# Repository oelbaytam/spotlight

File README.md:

# Spotlight

## What does it even do?
Spotlight is an [MQTT](https://learn.sparkfun.com/tutorials/introduction-to-mqtt/all) activated semi-high power LED (3.3-3.6V @715mA). It connects to MQTT Brokers (stay tuned for an MQTT discord bot!!) and uses the signal recieved to enable a PWM output to the LED. If I get it working correctly then there will be an enclosure with a way to focus the beam and some additional lenses to project imagery onto your wall or ceiling (think Bat-Signal). There are no physical inputs on the device so this is not a lamp.

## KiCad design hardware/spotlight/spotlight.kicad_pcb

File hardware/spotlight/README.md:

# The Spotlight Hardware

Spotlight is my first attempt at SMD soldering, PCB design, Circuitry implementing an IC, and many other smaller things, so bear with any mistakes I make and feel free to contribute if you have hardware knowledge! \
(Make sure you teach me something if you submit a PR >:] )

## The Schematic and PCB
##### Fraud at a glance?

### The ICs
- AL8841MP-13 \
  A buck converter stepping down the 5V input to ~714mA constant current configured by the 0.14Ohm sense resistor. The LED I am using is 5W and expects 3.6V at 1.2A but in my testing it was plenty bright at 700mA@3.3V so I decided that it will live its life at 3W (heatsinks really drove up the price per unit).
- AMS1117-3.3 \
  LDO regulator that provides 3.3V to the MCU.
- ESP32-C3-WROOM-02-N4 \
  Before its a hardware project this was initially an embedded project so I could learn RTOS, MQTT, and the ESP-IDF development framework! I went with the WROOM because I only planned on using one GPIO pin. The C3 MINI was a bit cheaper but had a lot of much smaller pads that I wasn't confident I could reflow. (Probably could've added some extra pins but I didn't wanna overcomplicate any more.)

### The Cool Image on the Back?!
The picture is an item icon in DEADLOCK (I <3 Deadlock) called [Boundless Spirit](https://deadlock.wiki/Boundless_Spirit). It has nothing to do with the project, just a cool stamp I snatched. I put it through some image dithering so that it can work with the silkscreen, when I get the first PCBs in I will put a picture of it to show the real world result.

# Assembling the device
I don't know yet, but I have a plan that I will share with anyone who is new so assembly can be easy and cheap, I am pinching as many pennies as possible with this project. (Possibly will make a video?)

### Parts List

As of now, to get flashbanged, all you need is:
- The materials in the BOM (in the ./production folder but I would export it yourself)
- 3.3V LED that wont die taking 750mA (technically the size doesn't matter yet since I don't have an enclosure made.)
- JST XH-2 connector with a cable
- a Heatsink for the LED, I am going to use a 40x40x11mm heatsink. 
I am going to put my bead LED on a little star aluminum PCB to make my life easier and to make heat transfer to the heatsink better.

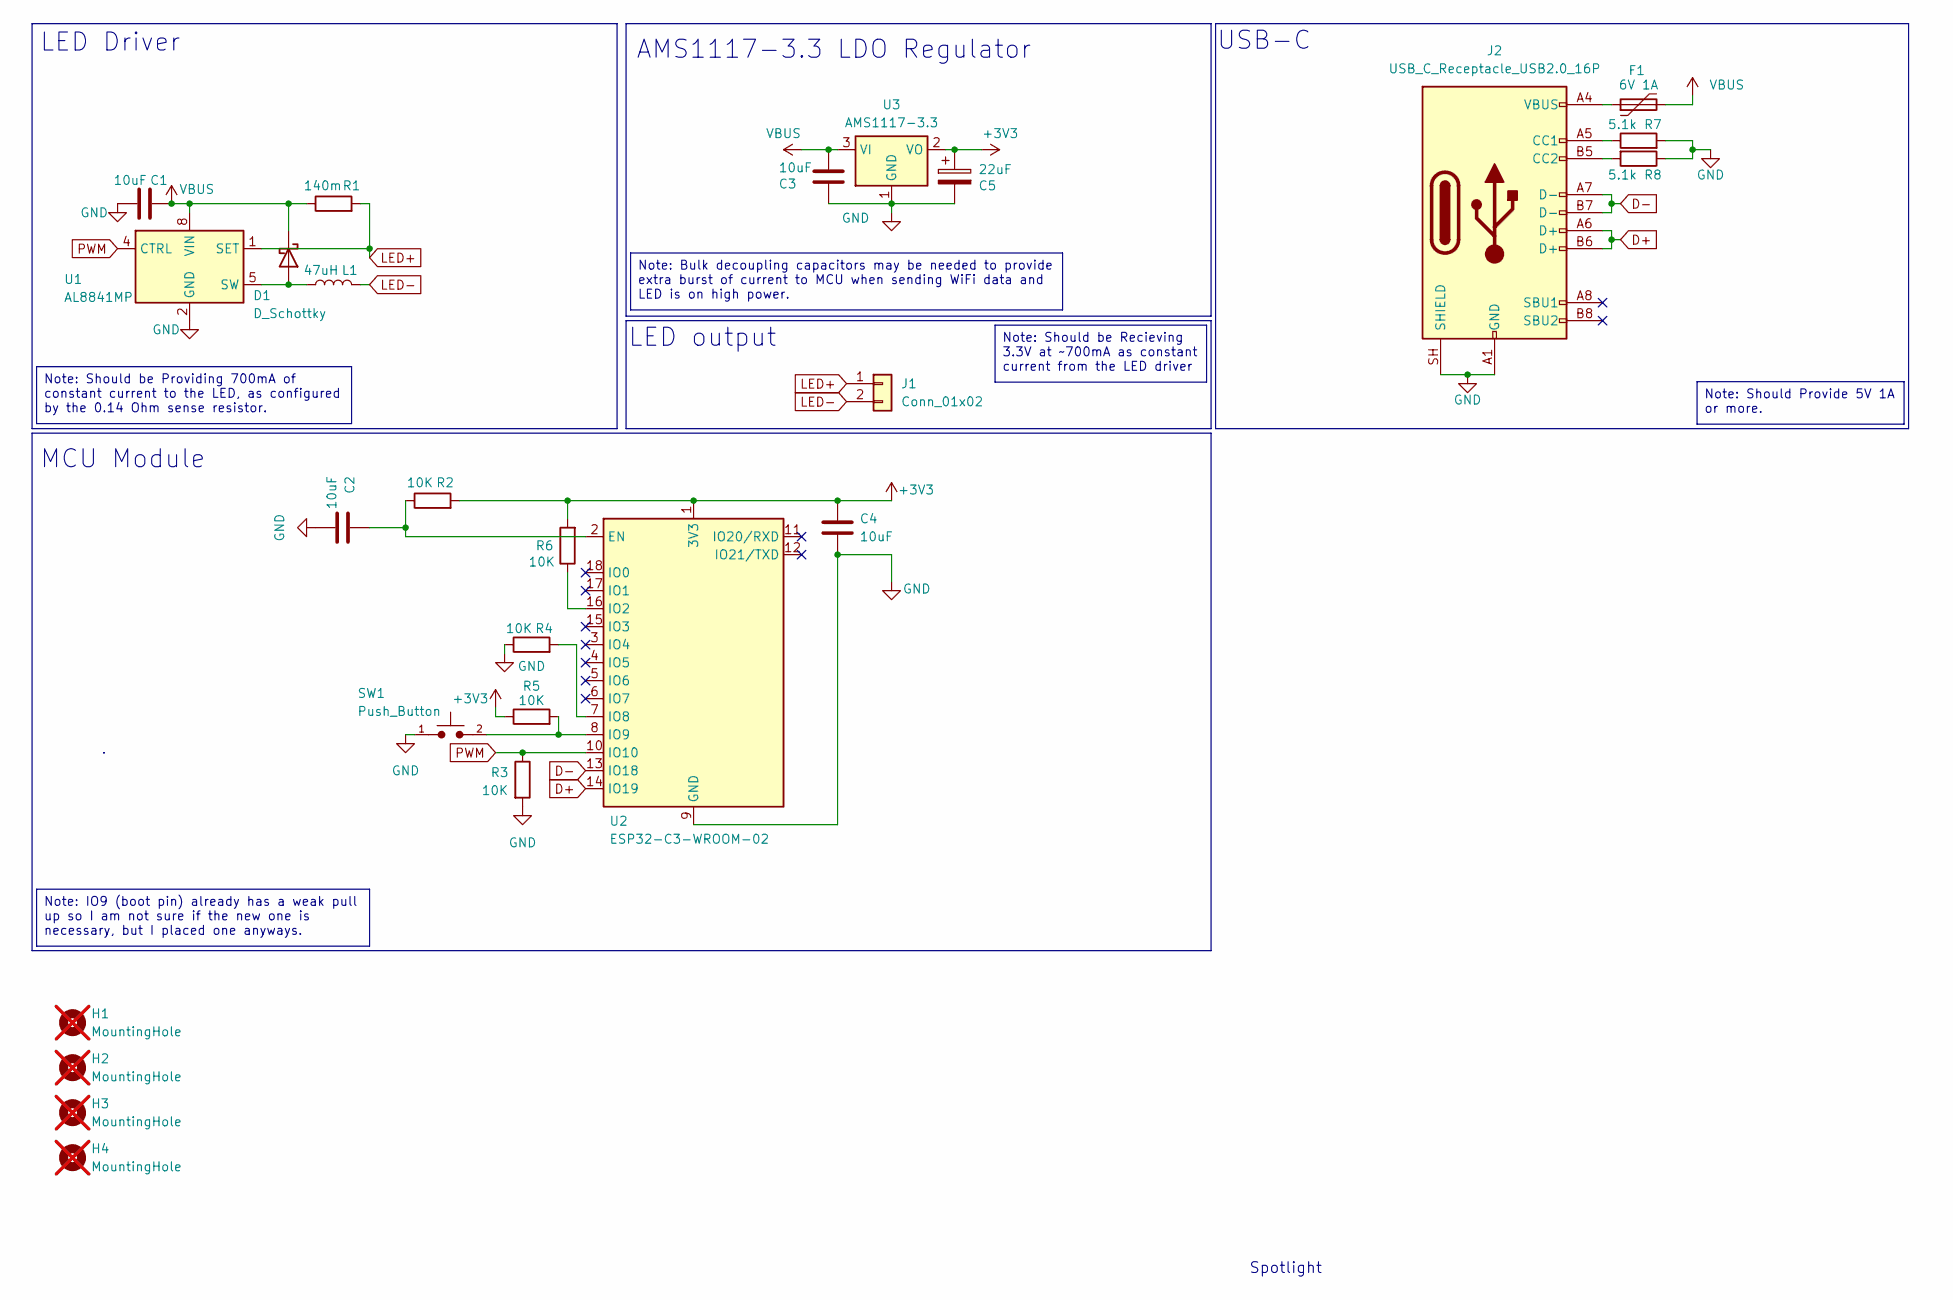
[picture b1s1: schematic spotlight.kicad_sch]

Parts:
C1, C2, C3, C4: 10uF; C_0603_1608Metric
C5: 22uF; C_1206_3216Metric
D1: D_Schottky; D_SOD-123F
F1: 6V 1A; R_0805_2012Metric
H1, H2, H3, H4: MountingHole; MountingHole_2.1mm; not fitted
J1: Conn_01x02; JST_XH_B2B-XH-A_1x02_P2.50mm_Vertical
J2: USB_C_Receptacle_USB2.0_16P; USB_C_Receptacle_XKB_U262-16XN-4BVC11
L1: 47uH; L_Chilisin_BWVS00606020
R1: 140m; R_1206_3216Metric
R2, R3, R4, R5, R6: 10K; R_0603_1608Metric
R7, R8: 5.1k; R_0603_1608Metric
SW1: Push_Button; SW_SPST_Omron_B3F-315x_Angled
U1: AL8841MP; MSOP-8-1EP_3x3mm_P0.65mm_EP1.5x1.8mm
U2: ESP32-C3-WROOM-02
U3: AMS1117-3.3; SOT-223-3_TabPin2

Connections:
+3V3: C4.1, C5.1, R2.2, R5.1, R6.2, U2.1 (3V3), U3.2 (VO)
D+: J2.A6 (D+), J2.B6 (D+), U2.14 (IO19)
D-: J2.A7 (D-), J2.B7 (D-), U2.13 (IO18)
GND: C1.2, C2.2, C3.2, C4.2, C5.2, J2.A1 (GND), J2.A12 (GND), J2.B1 (GND), J2.B12 (GND), J2.SH (SHIELD), R3.2, R4.1, R7.2, R8.1, SW1.1, U1.2 (GND), U1.3 (GND), U1.9 (GND), U2.9 (GND), U2.19 (GND), U3.1 (GND)
LED+: J1.1, R1.2, U1.1 (SET)
LED-: J1.2, L1.2
unnamed: D1.2 (A), L1.1, U1.5 (SW), U1.6 (SW)
unnamed: F1.1, J2.A4 (VBUS), J2.A9 (VBUS), J2.B4 (VBUS), J2.B9 (VBUS)
unnamed: J2.A5 (CC1), R7.1
unnamed: J2.B5 (CC2), R8.2
unnamed: C2.1, R2.1, U2.2 (EN)
unnamed: R6.1, U2.16 (IO2)
unnamed: R4.2, U2.7 (IO8)
unnamed: R5.2, SW1.2, U2.8 (IO9)
PWM: R3.1, U1.4 (CTRL), U2.10 (IO10)
VBUS: C1.1, C3.1, D1.1 (K), F1.2, R1.1, U1.8 (VIN), U3.3 (VI)

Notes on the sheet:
LED output
AMS1117-3.3 LDO Regulator
MCU Module
Spotlight
USB-C
LED Driver
Note: Bulk decoupling capacitors may be needed to provide extra burst of current to MCU when sending WiFi data and LED is on high power.
Note: IO9 (boot pin) already has a weak pull up so I am not sure if the new one is necessary, but I placed one anyways.
Note: Should be Providing 700mA of constant current to the LED, as configured by the 0.14 Ohm sense resistor.
Note: Should Provide 5V 1A or more.
Note: Should be Recieving 3.3V at ~700mA as constant current from the LED driver

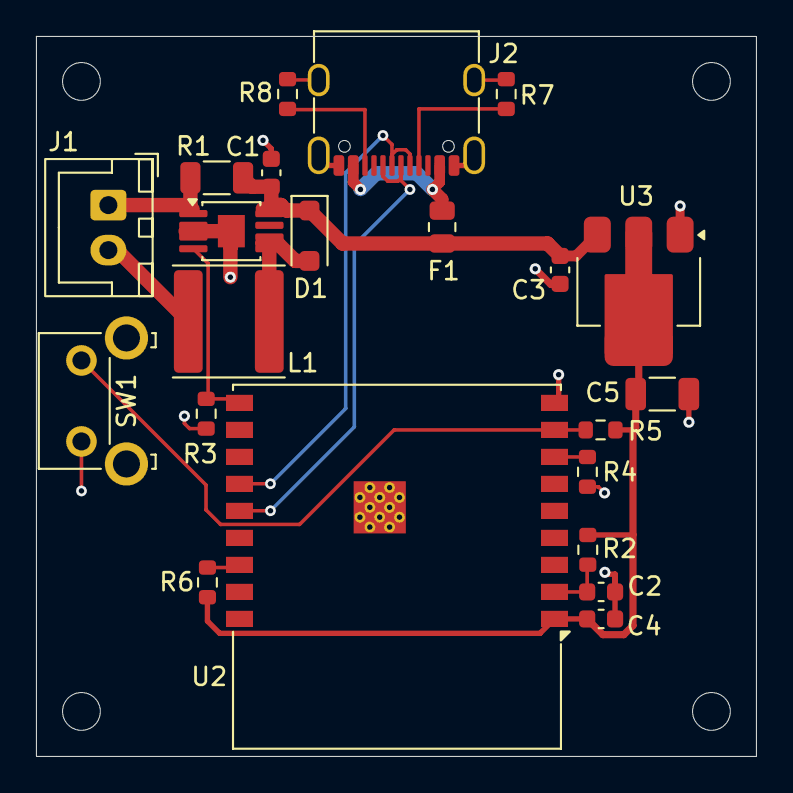
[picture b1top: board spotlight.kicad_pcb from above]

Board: 2 copper layers, 40.0 x 40.0 mm, 26 parts (0 on the bottom side), 16 nets.

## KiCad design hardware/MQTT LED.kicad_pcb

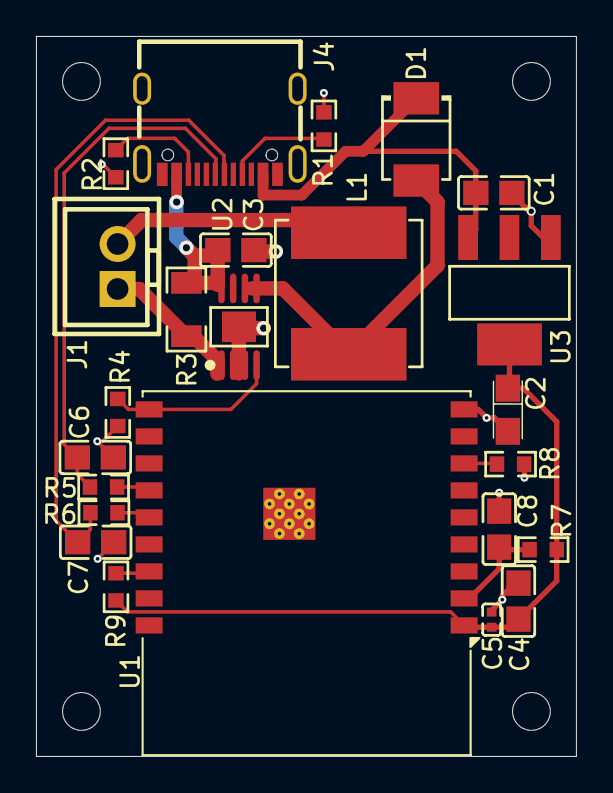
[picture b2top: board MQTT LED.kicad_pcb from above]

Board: 2 copper layers, 30.0 x 40.0 mm, 28 parts (0 on the bottom side), 16 nets.

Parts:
C1, C3, C4: 10uF; C0805
C2: 22uF; CASE-A_3216
C5: 100nF; C0402
C6, C7: C; C0805
C8: 1uF; C0805
D1: D_Schottky; SMBF_L4.3-W3.6-LS5.3-RD
H1, H2, H3, H4: MountingHole; MountingHole_2.1mm
J1: 1x2P; CONN-TH_XH-2A_C722856
J4: USB_C_Receptacle_USB2.0_16P; TYPE-C-SMD_TYPE-C-3.1-16PIN
L1: 47uH; IND-SMD_L8.0-W8.0_ESN8040
R1, R2: 5.1K; R0603
R3: 100m; R1206
R4, R7, R8, R9: 10K; R0603
R5, R6: R; R0603
U1: ESP32-C3-WROOM-02
U2: AL8860QMP-13; MSOP-8_L3.0-W3.0-P0.65-LS4.9-BL-EP
U3: AMS1117-3.3; SOT-223-3_L6.5-W3.4-P2.30-LS7.0-BR

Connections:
+3V3: C2.1, C4.1, C5.1, R7.2, R9.2, U1.1 (3V3), U3.4 (VOUT)
D+: C7.1, J4.A6 (D+), R6.1
D-: C6.1, J4.A7 (D-), R5.1
GND: C1.1, C2.2, C3.1, C4.2, C5.2, C6.2, C7.2, C8.1, R1.1, R2.2, R4.2, R8.1, U1.9 (GND), U1.19 (GND), U2.2 (GND), U2.3 (GND), U2.9 (EP), U3.1 (GND)
LED+: J1.1, R3.1, U2.1 (SET)
LED-: J1.2, L1.1
unnamed: D1.2 (A), L1.2, U2.5 (SW), U2.6 (SW)
unnamed: J4.A5 (CC1), R1.2
unnamed: J4.B5 (CC2), R2.1
unnamed: C8.2, R7.1, U1.2 (EN)
unnamed: R9.1, U1.16 (IO2)
unnamed: R8.2, U1.7 (IO8)
unnamed: R5.2, U1.13 (IO18)
unnamed: R6.2, U1.14 (IO19)
PWM: R4.1, U1.10 (IO10), U2.4 (CTRL)
VBUS: C1.2, C3.2, D1.1 (K), J4.A4B9 (VBUS), J4.B4A9 (VBUS), R3.2, U2.8 (VIN), U3.3 (VIN)

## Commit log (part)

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2026-06-22 Initialized ESP-IDF Firmware and KiCAD Project with Core IC's and Outputs
2026-06-24 v1 of the board?
2026-06-24 PCB updates
2026-06-28 added todos
2026-06-28 Switched to USB programming and ESP32-C3 module
